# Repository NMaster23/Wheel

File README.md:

# Wheel
An STM32F407VGT6 based microcontroller board designed for use with the OpenFFBoard firmware.
This is made to be used as a controller for a hoverboard hub motor. That way you can use the hoverboard for direct drive sim racing.

## Setup
This controller will be flashed with the OpenFFBoard firmware over the dedicated ST-Link port. It is the unlabeled 1 x 5 connector. I will then flash the hoverboard with: . This will then allow me to use the hoverboard as a regular BLDC motor thus allowing me to create a fully working sim wheel.

## BOM
This design requires a lot of parts. So there are 3 places the parts need to be bought from. Ebay for the motor itself, I am using a motherboard I already have that I have verified works with this.
Wheel V3 CSV: 
Wheel Brake CSV: 

Motor: 
PCB: 
Miscellaneous Components: 

### BOM Screenshots:
Motor: 
PCB: 
Miscellaneous Components: 

## Design

This is a picture of the full schematic:

This is a picture of the board for the MT6835 magnetic encoder:

This is a picture of the board for the Brake Chopper:

This is a picture of the full PCB:

This is a picture of the Brake Chopper PCB:

This is a picture of the expected product, but missing a few footprints:

This is a picture of the expected Brake Chopper:

## Why
I decided to try and make this project because ever since I was a kid I have always loved racing and playing racing games. I just could not afford to buy the actual wheel to play it on. And when one of my friends told me about Hack Club I got the opportunity to make what I want instead of just buying it off the shelf turning it into a learning experience. This has all come together for my wheel project with my hours of research and development coming together for this.

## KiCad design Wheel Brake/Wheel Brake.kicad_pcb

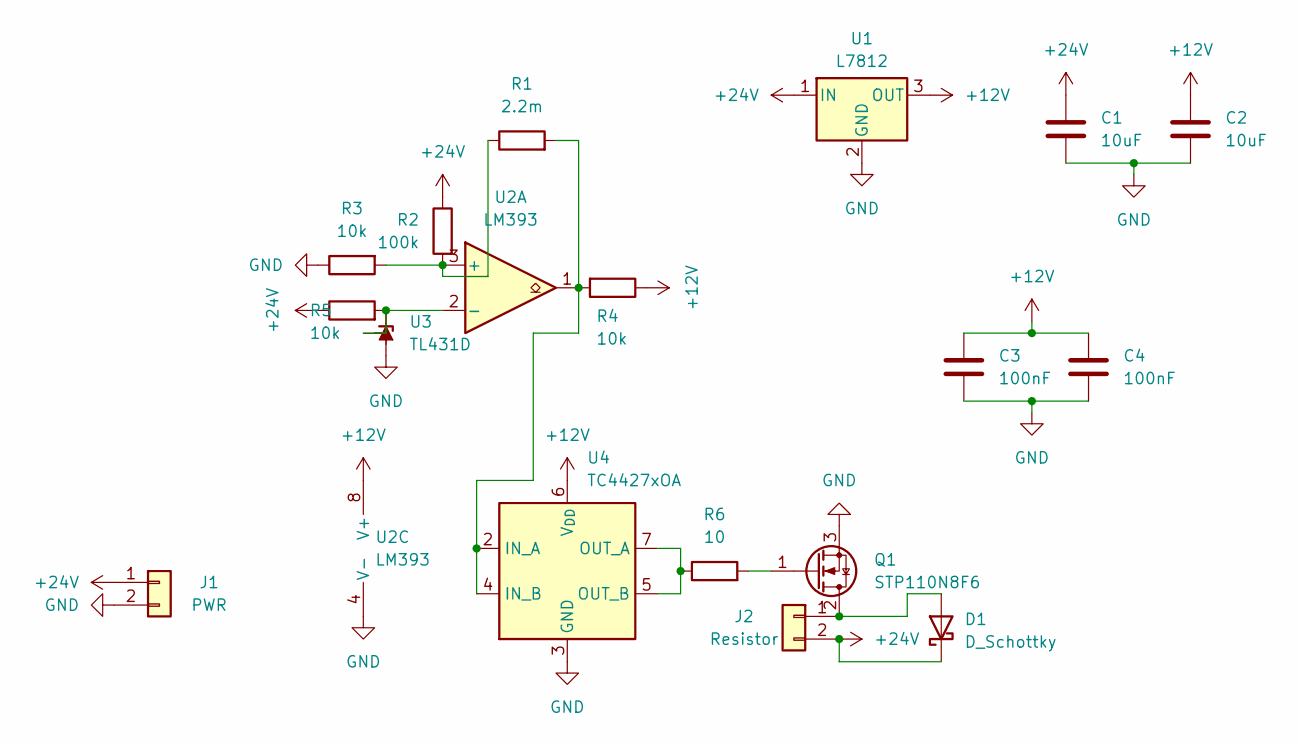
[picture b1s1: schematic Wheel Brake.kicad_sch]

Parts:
C1, C2: 10uF; C_0805_2012Metric
C3, C4: 100nF; C_0805_2012Metric
D1: D_Schottky; TO-220-2_Vertical
J1: PWR; AMASS_XT60-M_1x02_P7.20mm_Vertical
J2: Resistor; AMASS_XT60-M_1x02_P7.20mm_Vertical
Q1: STP110N8F6; TO-220-3_Vertical
R1: 2.2m; R_0805_2012Metric
R2: 100k; R_0805_2012Metric
R3, R4, R5: 10k; R_0805_2012Metric
R6: 10; R_0805_2012Metric
U1: L7812; Converter_DCDC_RECOM_R-78E-0.5_THT
U2: LM393; SOIC-8_3.9x4.9mm_P1.27mm
U3: TL431D; SOIC-8_3.9x4.9mm_P1.27mm
U4: TC4427xOA; SOIC-8_3.9x4.9mm_P1.27mm

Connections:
+12V: C2.1, C3.1, C4.1, R4.1, U1.3 (OUT), U2.8 (V+), U4.6 (V_{DD})
+24V: C1.1, D1.1 (K), J1.1, J2.2, R2.1, R5.1, U1.1 (IN)
GND: C1.2, C2.2, C3.2, C4.2, J1.2, Q1.3 (S), R3.1, U1.2 (GND), U2.4 (V-), U3.2 (A), U3.3 (A), U3.6 (A), U3.7 (A), U4.3 (GND)
unnamed: D1.2 (A), J2.1, Q1.2 (D)
unnamed: Q1.1 (G), R6.2
unnamed: R1.1, R2.2, R3.2, U2.3 (+)
unnamed: R5.2, U2.2 (-), U3.1 (K), U3.8 (REF)
unnamed: R1.2, R4.2, U2.1, U4.2 (IN_A), U4.4 (IN_B)
unnamed: R6.1, U4.5 (OUT_B), U4.7 (OUT_A)

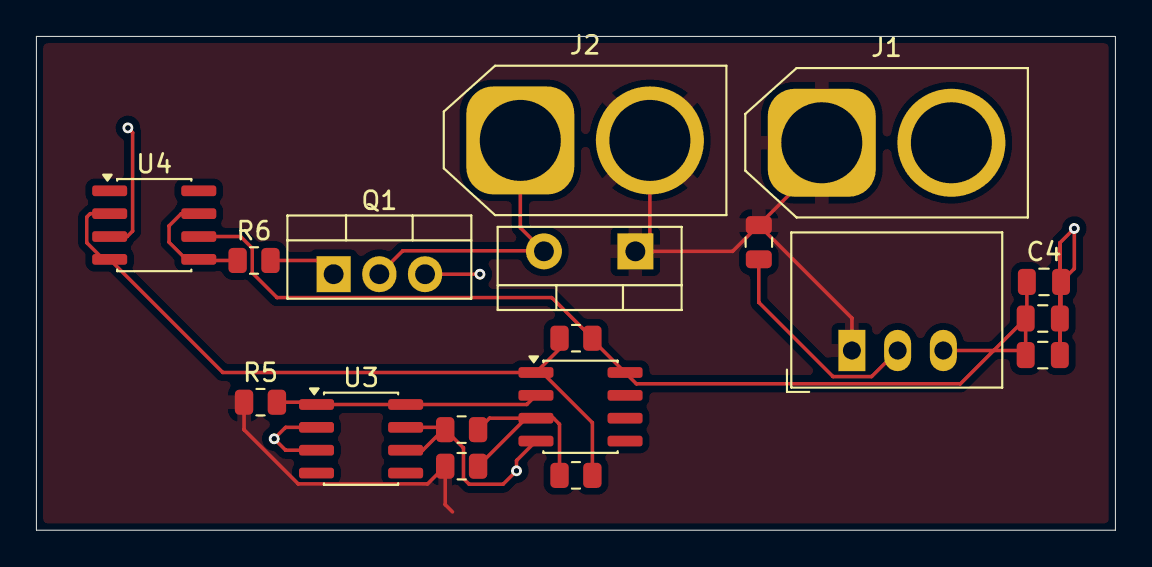
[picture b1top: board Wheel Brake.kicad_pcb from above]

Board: 2 copper layers, 59.9 x 27.4 mm, 18 parts (0 on the bottom side), 9 nets.

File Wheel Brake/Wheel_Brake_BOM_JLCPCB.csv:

Comment,Designator,Footprint,LCSC Part #
10uF,"C1,C2",C_0805_2012Metric,C15850
100nF,"C3,C4",C_0805_2012Metric,C49678
D_Schottky - NEEDS PART SELECTION,D1,TO-220-2_Vertical,TBD
PWR (XT60 Male),J1,AMASS_XT60-M_1x02_P7.20mm_Vertical,C98733
Resistor Tap (XT60 Male),J2,AMASS_XT60-M_1x02_P7.20mm_Vertical,C98733
STP110N8F6,Q1,TO-220-3_Vertical,C81146
2.2mOhm Shunt - NEEDS SOURCING,R1,R_0805_2012Metric,TBD
100k,R2,R_0805_2012Metric,C17407
10k,"R3,R4,R5",R_0805_2012Metric,C17414
10 - VERIFY VALUE,R6,R_0805_2012Metric,TBD
R-78E12-0.5 (DC/DC 24V->12V) - NOT STOCKED,U1,Converter_DCDC_RECOM_R-78E-0.5_THT,TBD
LM393,U2,SOIC-8_3.9x4.9mm_P1.27mm,C136033
TL431ACDT,U3,SOIC-8_3.9x4.9mm_P1.27mm,C6969
TC4427AEOA,U4,SOIC-8_3.9x4.9mm_P1.27mm,C18690

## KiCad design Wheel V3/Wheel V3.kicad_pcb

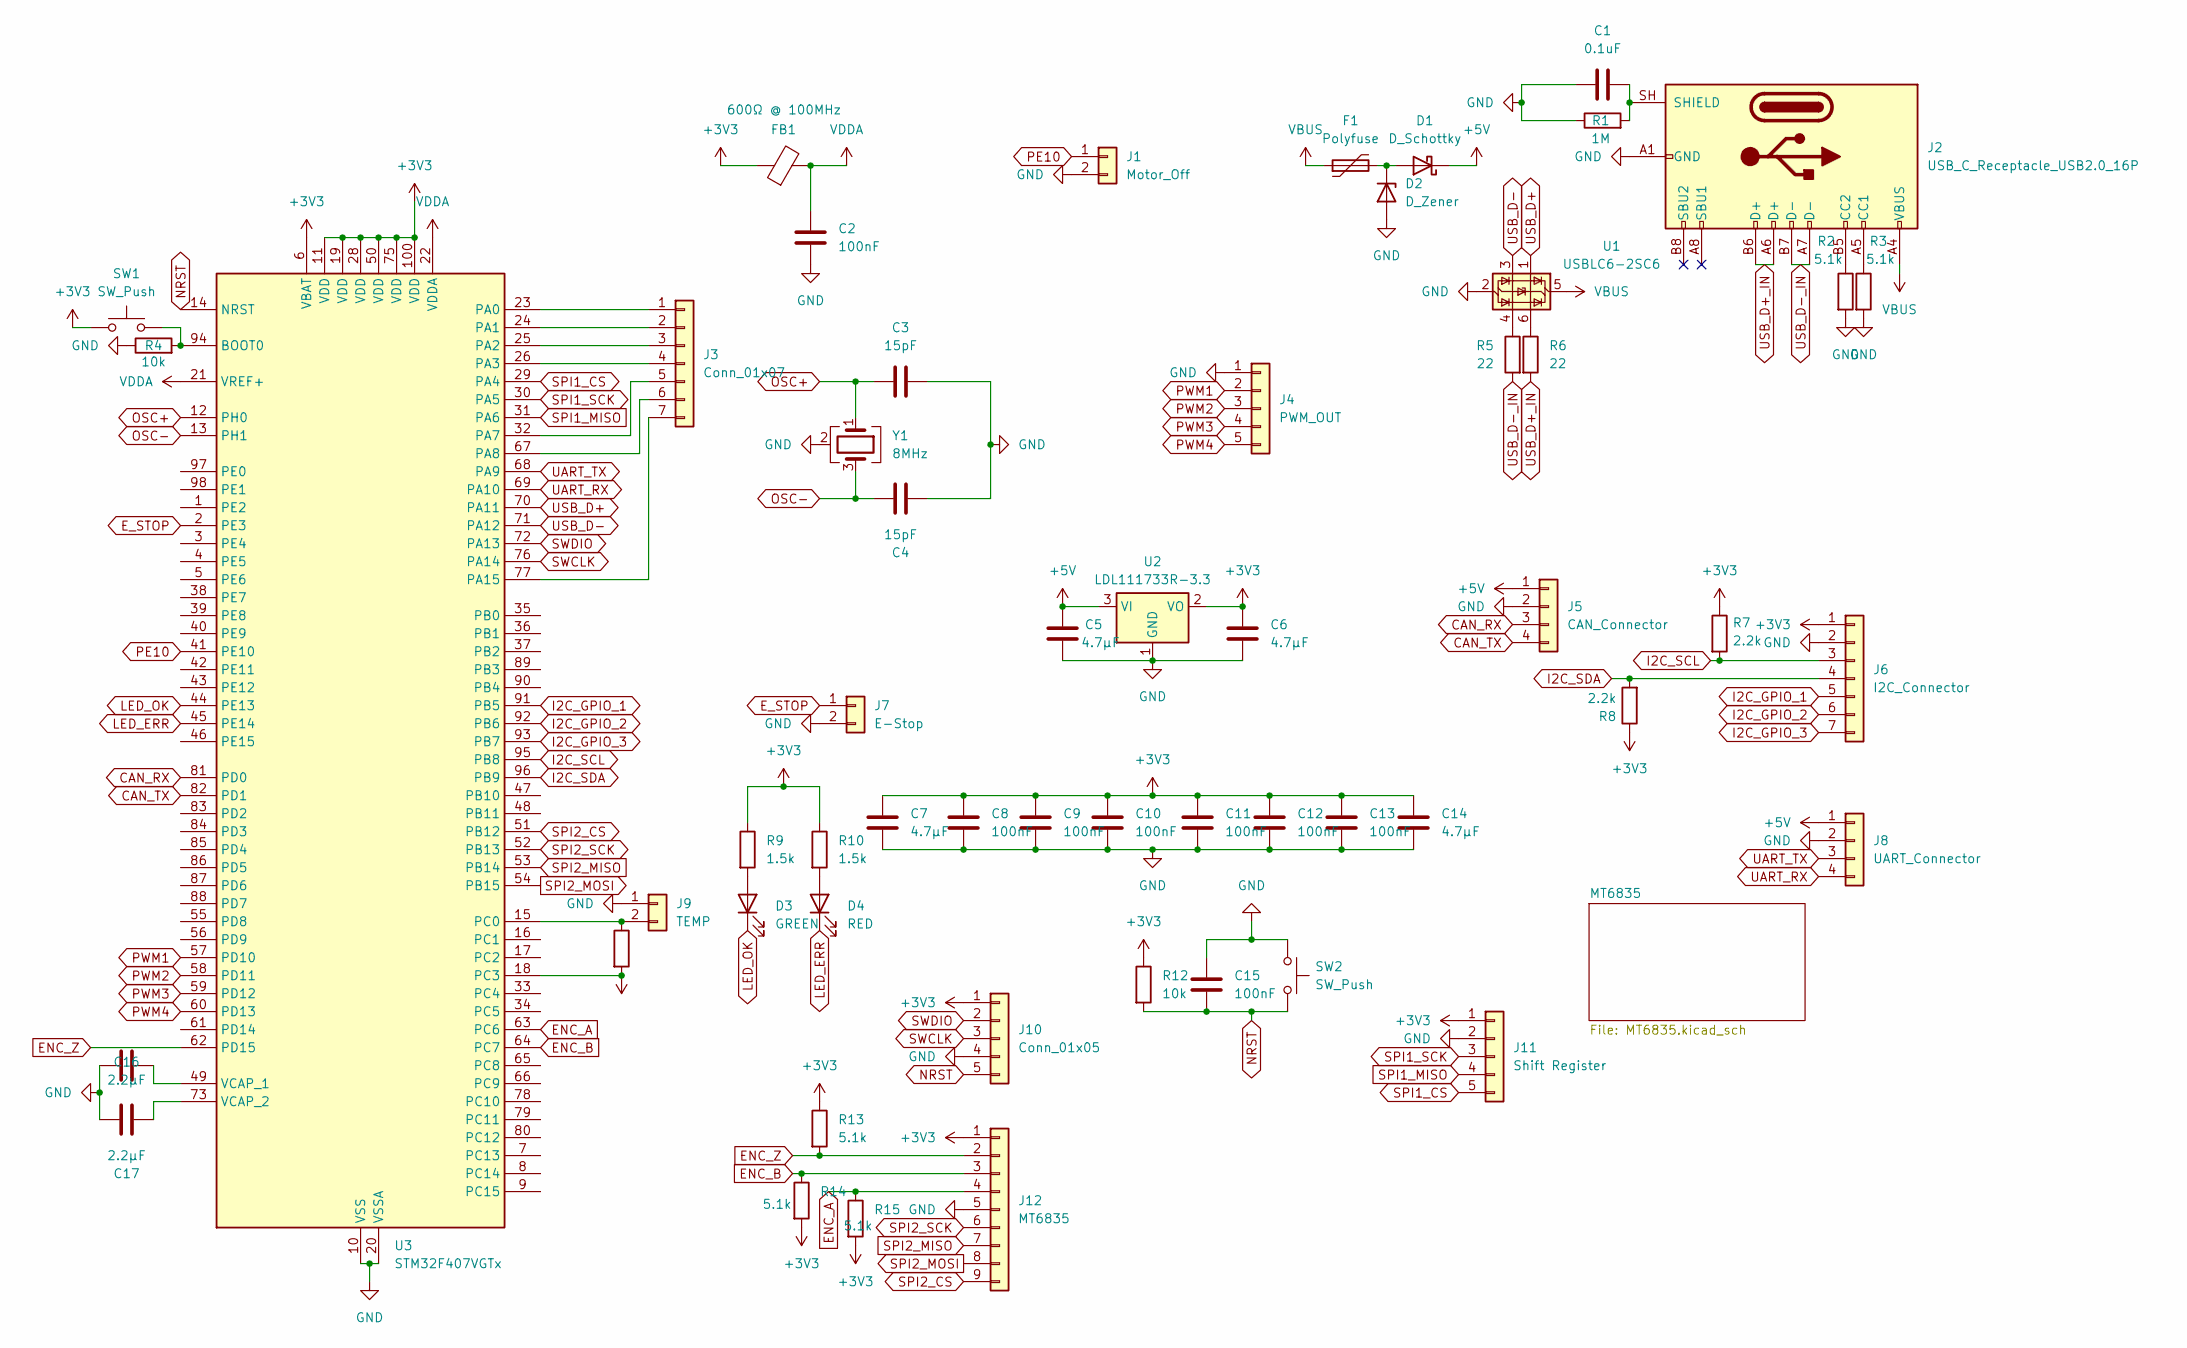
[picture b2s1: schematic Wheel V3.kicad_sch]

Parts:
C1: 0.1uF; C_0805_2012Metric
C2, C8, C9, C10, C11, C12, C13, C15: 100nF; C_0805_2012Metric
C3, C4: 15pF; C_0805_2012Metric
C5, C6, C7, C14: 4.7µF; C_0805_2012Metric
C16, C17: 2.2µF; C_0805_2012Metric
D1: D_Schottky; D_SOD-123
D2: D_Zener; D_SOD-123
D3: GREEN; LED_0805_2012Metric
D4: RED; LED_0805_2012Metric
F1: Polyfuse; Fuse_1206_3216Metric
FB1: 600Ω @ 100MHz; L_0805_2012Metric
J1: Motor_Off; JST_XH_B2B-XH-A_1x02_P2.50mm_Vertical
J2: USB_C_Receptacle_USB2.0_16P; USB_C_Receptacle_HRO_TYPE-C-31-M-12
J3: Conn_01x07; JST_XH_B7B-XH-A_1x07_P2.50mm_Vertical
J4: PWM_OUT; JST_XH_B5B-XH-A_1x05_P2.50mm_Vertical
J5: CAN_Connector; JST_XH_B4B-XH-A_1x04_P2.50mm_Vertical
J6: I2C_Connector; JST_XH_B7B-XH-A_1x07_P2.50mm_Vertical
J7: E-Stop; JST_XH_B2B-XH-A_1x02_P2.50mm_Vertical
J8: UART_Connector; JST_XH_B4B-XH-A_1x04_P2.50mm_Vertical
J9: TEMP; JST_XH_B2B-XH-A_1x02_P2.50mm_Vertical
J10: Conn_01x05; JST_XH_B5B-XH-A_1x05_P2.50mm_Vertical
J11: Shift Register; JST_XH_B5B-XH-A_1x05_P2.50mm_Vertical
J12: MT6835; JST_XH_B9B-XH-A_1x09_P2.50mm_Vertical
R1: 1M; R_0805_2012Metric
R2, R3, R13, R14, R15: 5.1k; R_0805_2012Metric
R4, R11, R12: 10k; R_0805_2012Metric
R5, R6: 22; R_0805_2012Metric
R7, R8: 2.2k; R_0805_2012Metric
R9, R10: 1.5k; R_0805_2012Metric
SW1, SW2: SW_Push; SW_SPST_B3U-1000P
U1: USBLC6-2SC6; SOT-23-6
U2: LDL111733R-3.3; SOT-223-3_TabPin2
U3: STM32F407VGTx; LQFP-100_14x14mm_P0.5mm
Y1: 8MHz; Crystal_SMD_5032-4Pin_5.0x3.2mm

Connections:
+3V3: C6.1, C7.1, C8.1, C9.1, C10.1, C11.1, C12.1, C13.1, C14.1, FB1.1, J6.1, J10.1, J11.1, J12.1, R7.1, R8.1, R9.1, R10.1, R11.2, R12.1, R13.1, R14.2, R15.2, SW1.1, U2.2 (VO), U3.6 (VBAT), U3.11 (VDD), U3.18 (PC3), U3.19 (VDD), U3.28 (VDD), U3.50 (VDD), U3.75 (VDD), U3.100 (VDD)
+5V: C5.1, D1.1 (K), J5.1, J8.1, U2.3 (VI)
CAN_RX: J5.3, U3.81 (PD0)
CAN_TX: J5.4, U3.82 (PD1)
ENC_A: J12.4, R15.1, U3.63 (PC6)
ENC_B: J12.3, R14.1, U3.64 (PC7)
ENC_Z: J12.2, R13.2, U3.62 (PD15)
E_STOP: J7.1, U3.2 (PE3)
GND: C1.2, C2.2, C3.2, C4.2, C5.2, C6.2, C7.2, C8.2, C9.2, C10.2, C11.2, C12.2, C13.2, C14.2, C15.1, C16.1, C17.1, D2.2 (A), J1.2, J2.A1 (GND), J2.A12 (GND), J2.B1 (GND), J2.B12 (GND), J4.1, J5.2, J6.2, J7.2, J8.2, J9.1, J10.4, J11.2, J12.5, R1.1, R2.2, R3.2, R4.1, SW2.1, U1.2 (GND), U2.1 (GND), U3.10 (VSS), U3.20 (VSSA), U3.27 (VSS), U3.74 (VSS), U3.99 (VSS), Y1.2 (G), Y1.4 (G); also elsewhere on the board
I2C_GPIO_1: J6.5, U3.91 (PB5)
I2C_GPIO_2: J6.6, U3.92 (PB6)
I2C_GPIO_3: J6.7, U3.93 (PB7)
I2C_SCL: J6.3, R7.2, U3.95 (PB8)
I2C_SDA: J6.4, R8.2, U3.96 (PB9)
LED_ERR: D4.1 (K), U3.45 (PE14)
LED_OK: D3.1 (K), U3.44 (PE13)
NRST: C15.2, J10.5, R12.2, SW2.2, U3.14 (NRST)
unnamed: D1.2 (A), D2.1 (K), F1.2
unnamed: D3.2 (A), R9.2
unnamed: D4.2 (A), R10.2
unnamed: J2.A5 (CC1), R3.1
unnamed: J2.B5 (CC2), R2.1
unnamed: C1.1, J2.SH (SHIELD), R1.2
unnamed: J3.1, U3.23 (PA0)
unnamed: J3.2, U3.24 (PA1)
unnamed: J3.3, U3.25 (PA2)
unnamed: J3.4, U3.26 (PA3)
unnamed: J3.5, U3.32 (PA7)
unnamed: J3.6, U3.67 (PA8)
unnamed: J3.7, U3.77 (PA15)
unnamed: J9.2, R11.1, U3.15 (PC0)
unnamed: R5.1, U1.4 (I/O2)
unnamed: R6.1, U1.6 (I/O1)
unnamed: R4.2, SW1.2, U3.94 (BOOT0)
unnamed: C16.2, U3.49 (VCAP_1)
unnamed: C17.2, U3.73 (VCAP_2)
OSC+: C3.1, U3.12 (PH0), Y1.1
OSC-: C4.1, U3.13 (PH1), Y1.3
PE10: J1.1, U3.41 (PE10)
PWM1: J4.2, U3.57 (PD10)
PWM2: J4.3, U3.58 (PD11)
PWM3: J4.4, U3.59 (PD12)
PWM4: J4.5, U3.60 (PD13)
SPI1_CS: J11.5, U3.29 (PA4)
SPI1_MISO: J11.4, U3.31 (PA6)
SPI1_SCK: J11.3, U3.30 (PA5)
SPI2_CS: J12.9, U3.51 (PB12)
SPI2_MISO: J12.7, U3.53 (PB14)
SPI2_MOSI: J12.8, U3.54 (PB15)
SPI2_SCK: J12.6, U3.52 (PB13)
SWCLK: J10.3, U3.76 (PA14)
SWDIO: J10.2, U3.72 (PA13)
UART_RX: J8.4, U3.69 (PA10)
UART_TX: J8.3, U3.68 (PA9)
USB_D+: U1.1 (I/O1), U3.70 (PA11)
USB_D+_IN: J2.A6 (D+), J2.B6 (D+), R6.2
USB_D-: U1.3 (I/O2), U3.71 (PA12)
USB_D-_IN: J2.A7 (D-), J2.B7 (D-), R5.2
VBUS: F1.1, J2.A4 (VBUS), J2.A9 (VBUS), J2.B4 (VBUS), J2.B9 (VBUS), U1.5 (VBUS)
VDDA: C2.1, FB1.2, U3.21 (VREF+), U3.22 (VDDA)

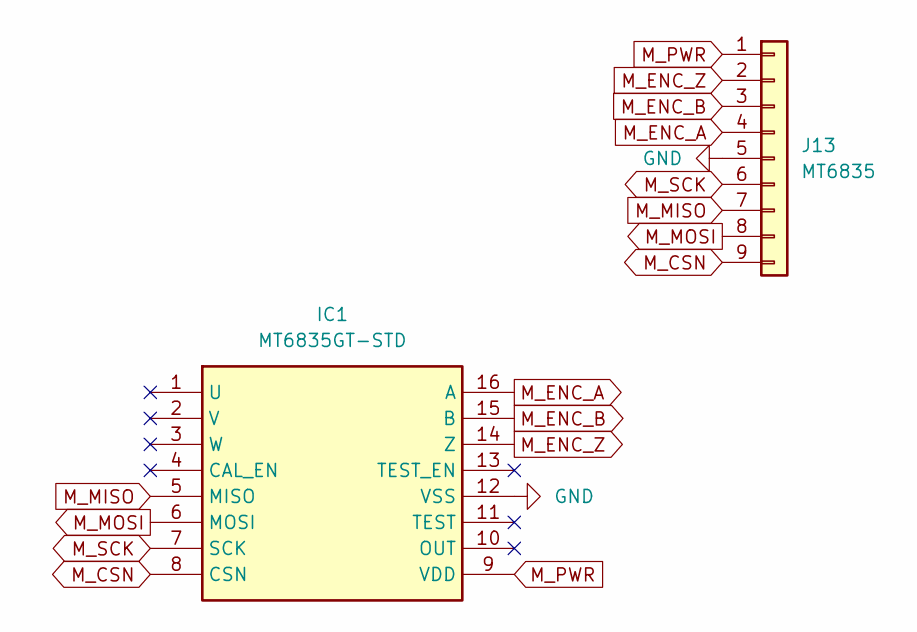
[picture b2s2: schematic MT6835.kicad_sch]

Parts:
IC1: MT6835GT-STD; SOP65P640X120-16N; Manufacturer_Part_Number MT6835GT-STD
J13: MT6835; JST_XH_B9B-XH-A_1x09_P2.50mm_Vertical

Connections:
GND: IC1.12 (VSS), J13.5; also elsewhere on the board
M_CSN: IC1.8 (CSN), J13.9
M_ENC_A: IC1.16 (A), J13.4
M_ENC_B: IC1.15 (B), J13.3
M_ENC_Z: IC1.14 (Z), J13.2
M_MISO: IC1.5 (MISO), J13.7
M_MOSI: IC1.6 (MOSI), J13.8
M_PWR: IC1.9 (VDD), J13.1
M_SCK: IC1.7 (SCK), J13.6

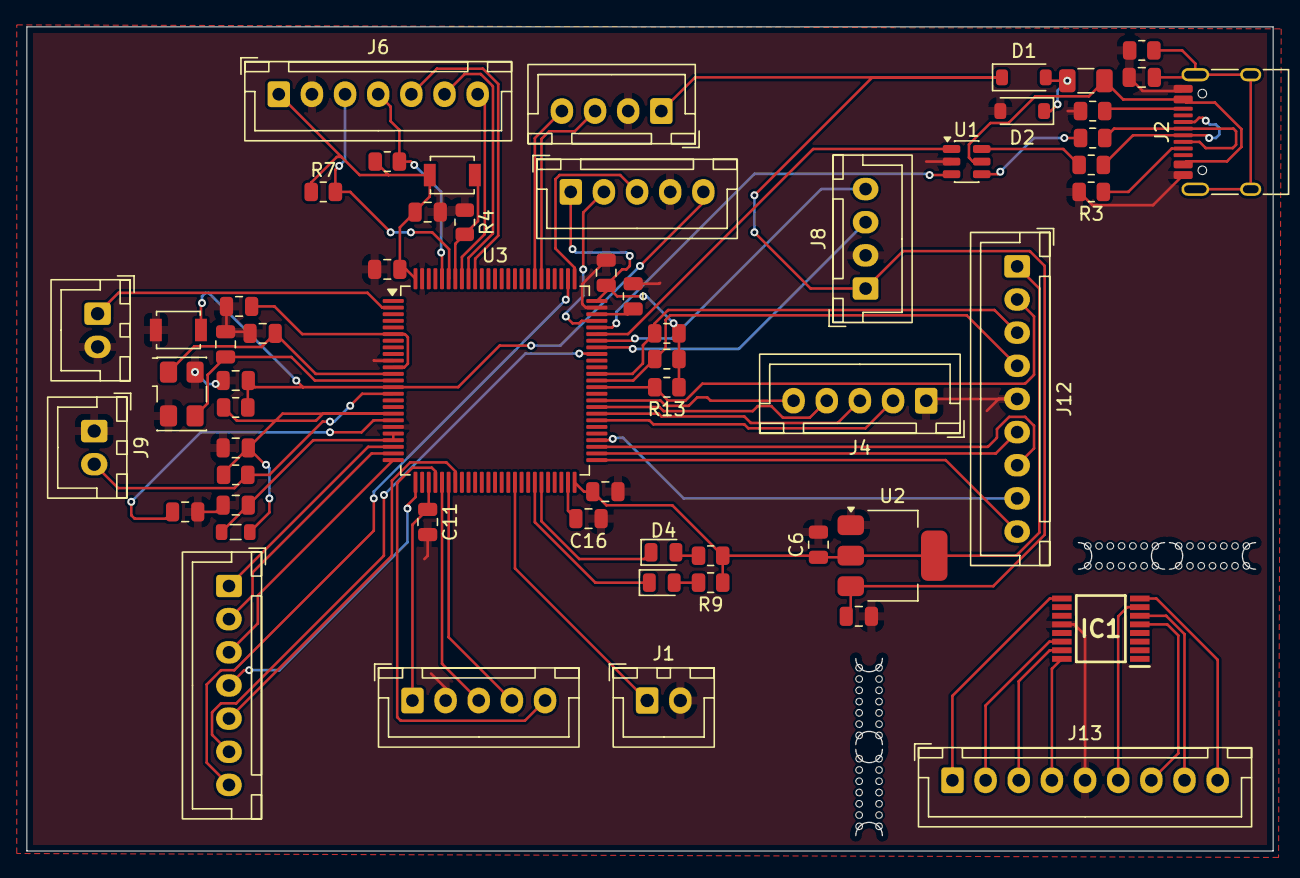
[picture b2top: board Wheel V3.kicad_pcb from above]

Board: 2 copper layers, 93.9 x 62.1 mm, 58 parts (0 on the bottom side), 68 nets.

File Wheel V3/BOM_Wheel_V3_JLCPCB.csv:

Comment,Designator,Footprint,LCSC Part #
0.1uF,C1,C_0805_2012Metric,C49678
100nF,"C2,C8,C9,C10,C11,C12,C13,C15",C_0805_2012Metric,C49678
15pF,"C3,C4",C_0805_2012Metric,C107110
4.7uF,"C5,C6,C7,C14",C_0805_2012Metric,C98195
2.2uF,"C16,C17",C_0805_2012Metric,C19110
D_Schottky,D1,D_SOD-123,C130887
D_Zener,D2,D_SOD-123,C2827905
GREEN,D3,LED_0805_2012Metric,C2297
RED,D4,LED_0805_2012Metric,C2295
Polyfuse,F1,Fuse_1206_3216Metric,C46641014
600ohm@100MHz,FB1,L_0805_2012Metric,C85837
MT6835GT-STD,IC1,SOP65P640X120-16N,C2932578
Motor_Off,J1,JST_XH_B2B-XH-A_1x02_P2.50mm_Vertical,C158012
USB_C_Receptacle_USB2.0_16P,J2,USB_C_Receptacle_HRO_TYPE-C-31-M-12,C165948
Conn_01x07,J3,JST_XH_B7B-XH-A_1x07_P2.50mm_Vertical,C144398
PWM_OUT,J4,JST_XH_B5B-XH-A_1x05_P2.50mm_Vertical,C157991
CAN_Connector,J5,JST_XH_B4B-XH-A_1x04_P2.50mm_Vertical,C144395
I2C_Connector,J6,JST_XH_B7B-XH-A_1x07_P2.50mm_Vertical,C144398
E-Stop,J7,JST_XH_B2B-XH-A_1x02_P2.50mm_Vertical,C158012
UART_Connector,J8,JST_XH_B4B-XH-A_1x04_P2.50mm_Vertical,C144395
TEMP,J9,JST_XH_B2B-XH-A_1x02_P2.50mm_Vertical,C158012
Conn_01x05,J10,JST_XH_B5B-XH-A_1x05_P2.50mm_Vertical,C157991
Shift Register,J11,JST_XH_B5B-XH-A_1x05_P2.50mm_Vertical,C157991
MT6835,"J12,J13",JST_XH_B9B-XH-A_1x09_P2.50mm_Vertical,C157966
1M,R1,R_0805_2012Metric,C17514
5.1k,"R2,R3,R13,R14,R15",R_0805_2012Metric,C27834
10k,"R4,R11,R12",R_0805_2012Metric,C17414
22,"R5,R6",R_0805_2012Metric,C17561
2.2k,"R7,R8",R_0805_2012Metric,C17520
1.5k,"R9,R10",R_0805_2012Metric,C4310
SW_Push,"SW1,SW2",SW_SPST_B3U-1000P,C231329
USBLC6-2SC6,U1,SOT-23-6,C2827654
LDL111733R-3.3,U2,SOT-223-3_TabPin2,C435835
STM32F407VGTx,U3,LQFP-100_14x14mm_P0.5mm,C12345
8MHz,Y1,Crystal_SMD_5032-4Pin_5.0x3.2mm,C157341

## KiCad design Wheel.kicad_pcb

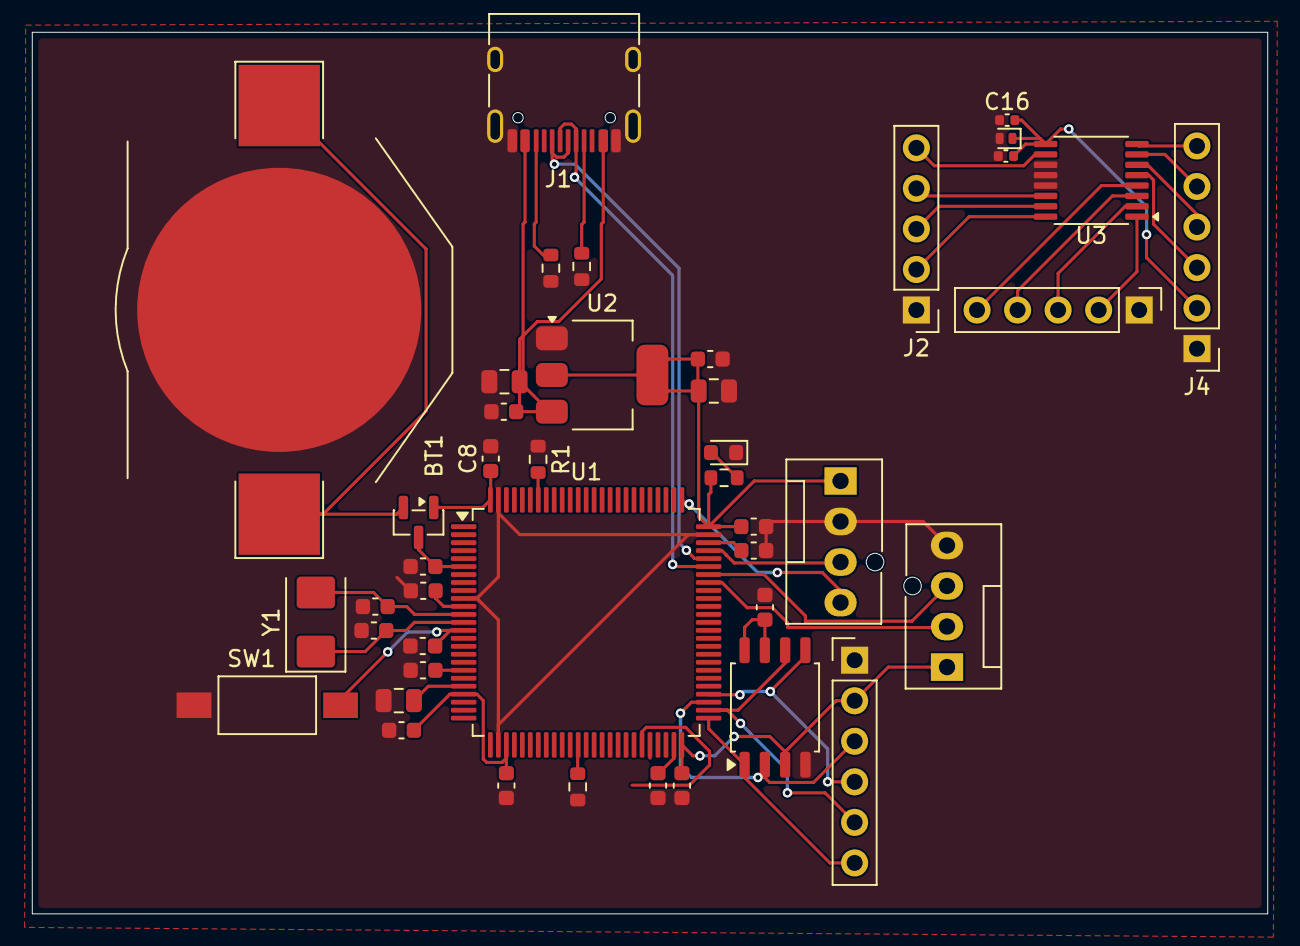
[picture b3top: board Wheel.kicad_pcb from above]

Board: 2 copper layers, 77.4 x 55.2 mm, 43 parts (0 on the bottom side), 42 nets.

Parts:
BT1: Battery; BatteryHolder_Keystone_3002_1x2032
C1, C2, C3, C4, C5, C6, C7, C8, C13, C17, C18, C19: 104; C_0603_1608Metric
C9, C12, C14: 106; C_0805_2012Metric
C10, C11: 2.2uF; C_0603_1608Metric
C15: 4.7µF; C_0402_1005Metric
C16: 0.1µF; C_0402_1005Metric
C20, C21: 20P; C_0603_1608Metric
D1: BDFN2A051U; D_SOD-882D
D2: LED; LED_0603_1608Metric
D3: BAT54C; SOT-23
J1: USB_C_Receptacle_USB2.0_14P; USB_C_Receptacle_HRO_TYPE-C-31-M-12
J2, J3: Conn_01x05; PinHeader_1x05_P2.54mm_Vertical
J4, J5: Conn_01x06; PinHeader_1x06_P2.54mm_Vertical
J6: Conn_01x04; FanPinHeader_1x04_P2.54mm_Vertical
J7: UART; FanPinHeader_1x04_P2.54mm_Vertical
R1: 10k; R_0603_1608Metric
R2, R3: 5.1k; R_0603_1608Metric
R4: 10K; R_0603_1608Metric
R5: 510R; R_0603_1608Metric
SW1: SW_Push; SW_SPST_FSMSM
U1: STM32F407VGTx; LQFP-100_14x14mm_P0.5mm
U2: AMS1117-3.3; SOT-223-3_TabPin2
U3: MT6835; TSSOP-16_4.4x5mm_P0.65mm
U4: W25Q16JVSS; SOIC-8_5.3x5.3mm_P1.27mm
Y1: 8MHz; Crystal_SMD_5032-2Pin_5.0x3.2mm

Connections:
+5V: C12.1, C13.1, J1.A4 (VBUS), J1.A9 (VBUS), J1.B4 (VBUS), J1.B9 (VBUS), U2.3 (VI)
A: J2.2, U3.16 (A)
B: J2.3, U3.15 (B)
CAL: J3.5, U3.4 (CAL_EN)
CS: U1.51 (PB12), U4.1 (~CS)
GND: BT1.2 (-), C1.1, C2.1, C3.2, C4.2, C5.2, C6.2, C7.2, C8.2, C9.2, C10.1, C11.1, C12.2, C13.2, C14.2, C15.1, C16.1, C17.2, C18.2, C19.1, C20.1, C21.1, D1.2 (A2), D2.1 (K), J1.A1 (GND), J1.A12 (GND), J1.B1 (GND), J1.B12 (GND), J1.SH (SHIELD), J2.1, J3.1, J4.1, J5.1, J6.2, J7.4, R1.1, R2.2, R3.2, R4.2, SW1.1, U1.10 (VSS), U1.27 (VSS), U1.74 (VSS), U1.99 (VSS), U2.1 (GND), U3.11 (TEST), U3.12 (GND), U3.13 (TEST_EN), U4.4 (GND)
MISO: U1.53 (PB14), U4.2 (DO/IO_{1})
MOSI: U1.54 (PB15), U4.5 (DI/IO_{0})
unnamed: BT1.1 (+), D3.2
unnamed: D2.2 (A), R5.2
unnamed: J1.A5 (CC1), R2.1
unnamed: J1.B5 (CC2), R3.1
unnamed: J4.3, U3.5 (MISO)
unnamed: J4.4, U3.6 (MOSI)
unnamed: J4.5, U3.7 (SCK)
unnamed: J4.6, U3.8 (CSN)
unnamed: J5.3, U1.31 (PA6)
unnamed: J5.4, U1.32 (PA7)
unnamed: J5.5, U1.30 (PA5)
unnamed: J5.6, U1.29 (PA4)
unnamed: J6.3, U1.72 (PA13)
unnamed: J6.4, U1.76 (PA14)
unnamed: R1.2, U1.94 (BOOT0)
unnamed: C1.2, SW1.2, U1.14 (NRST)
unnamed: R4.1, U1.37 (PB2)
unnamed: C10.2, U1.49 (VCAP_1)
unnamed: C11.2, U1.73 (VCAP_2)
unnamed: C19.2, U4.8 (VCC)
OSC_IN: C20.2, U1.12 (PH0), Y1.2
OSC_OUT: C21.2, U1.13 (PH1), Y1.1
PWM: J2.5, U3.10 (PWM_OUT)
RX_IN: J7.3, U1.69 (PA10)
SCK: U1.52 (PB13), U4.6 (CLK)
TX_OUT: J7.2, U1.68 (PA9)
U: J3.2, U3.1 (U)
USB_DM: J1.A7 (D-), J1.B7 (D-), U1.70 (PA11)
USB_DP: J1.A6 (D+), J1.B6 (D+), U1.71 (PA12)
V: J3.3, U3.2 (V)
VBAT: C18.1, D3.3, U1.6 (VBAT)
VDDA(1): C2.2, C3.1, C4.1, C5.1, C6.1, C7.1, C8.1, C9.1, C14.1, C15.2, C16.2, C17.1, D1.1 (A1), D3.1, J4.2, J5.2, J6.1, J7.1, R5.1, U1.11 (VDD), U1.19 (VDD), U1.21 (VREF+), U1.22 (VDDA), U1.28 (VDD), U1.50 (VDD), U1.75 (VDD), U1.100 (VDD), U2.2 (VO), U3.9 (VDD), U4.3 (~WP/IO_{2}), U4.7 (~HOLD/~RESET/IO_{3})
W: J3.4, U3.3 (W)
Z: J2.4, U3.14 (Z)

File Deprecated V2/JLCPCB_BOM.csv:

Designator,Comment,Footprint,LCSC Part Number
BT1,Battery,BatteryHolder_Keystone_3002_1x2032,
"C1, C2, C3, C4, C5, C6, C7, C8, C13, C17, C18, C19",104,C_0603_1608Metric,
"C9, C12, C14",106,C_0805_2012Metric,
"C10, C11",2.2uF,C_0603_1608Metric,
C15,4.7µF,C_0402_1005Metric,
C16,0.1µF,C_0402_1005Metric,
"C20, C21",20P,C_0603_1608Metric,
D1,BDFN2A051U,D_SOD-882D,
D2,LED,LED_0603_1608Metric,
D3,BAT54C,SOT-23,
J1,USB_C_Receptacle_USB2.0_14P,USB_C_Receptacle_HRO_TYPE-C-31-M-12,
"J2, J3",Conn_01x05,PinHeader_1x05_P2.54mm_Vertical,
"J4, J5",Conn_01x06,PinHeader_1x06_P2.54mm_Vertical,
J6,Conn_01x04,FanPinHeader_1x04_P2.54mm_Vertical,
J7,UART,FanPinHeader_1x04_P2.54mm_Vertical,
R1,10k,R_0603_1608Metric,
"R2, R3",5.1k,R_0603_1608Metric,
R4,10K,R_0603_1608Metric,
R5,510R,R_0603_1608Metric,
SW1,SW_Push,SW_SPST_FSMSM,
U1,STM32F407VGTx,LQFP-100_14x14mm_P0.5mm,
U2,AMS1117-3.3,SOT-223-3_TabPin2,
U3,MT6835,TSSOP-16_4.4x5mm_P0.65mm,
U4,W25Q16JVSS,SOIC-8_5.3x5.3mm_P1.27mm,
Y1,8MHz,Crystal_SMD_5032-2Pin_5.0x3.2mm,

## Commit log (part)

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2026-05-15 Implemented Most of the Schematic
2026-05-16 Finished Schematic
2026-05-26 Assets for ReadMe
2026-05-26 Update README with images of project components
    Added images of schematic, board, PCB, and expected product.
2026-06-25 Decided to retry for the final time
2026-06-30 Update image links in README
